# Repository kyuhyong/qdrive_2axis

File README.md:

# QDrive 2axis version

A 2 axis High current BLDC motor controller board based and compatible with Odrive project (https://github.com/madcowswe/ODriveHardware).

Part of this project is based from azmat's single channel BLDC controller board (https://github.com/azmat-bilal/bldc_motor_controller_pcb.git)

## Introduction

<div align="center">
  
</div>

## Odrive compatibility

This project is supposed to be compatible with odrive v3.6-56V.

## Announcement

This project is still in development and need modification to be working as expected.

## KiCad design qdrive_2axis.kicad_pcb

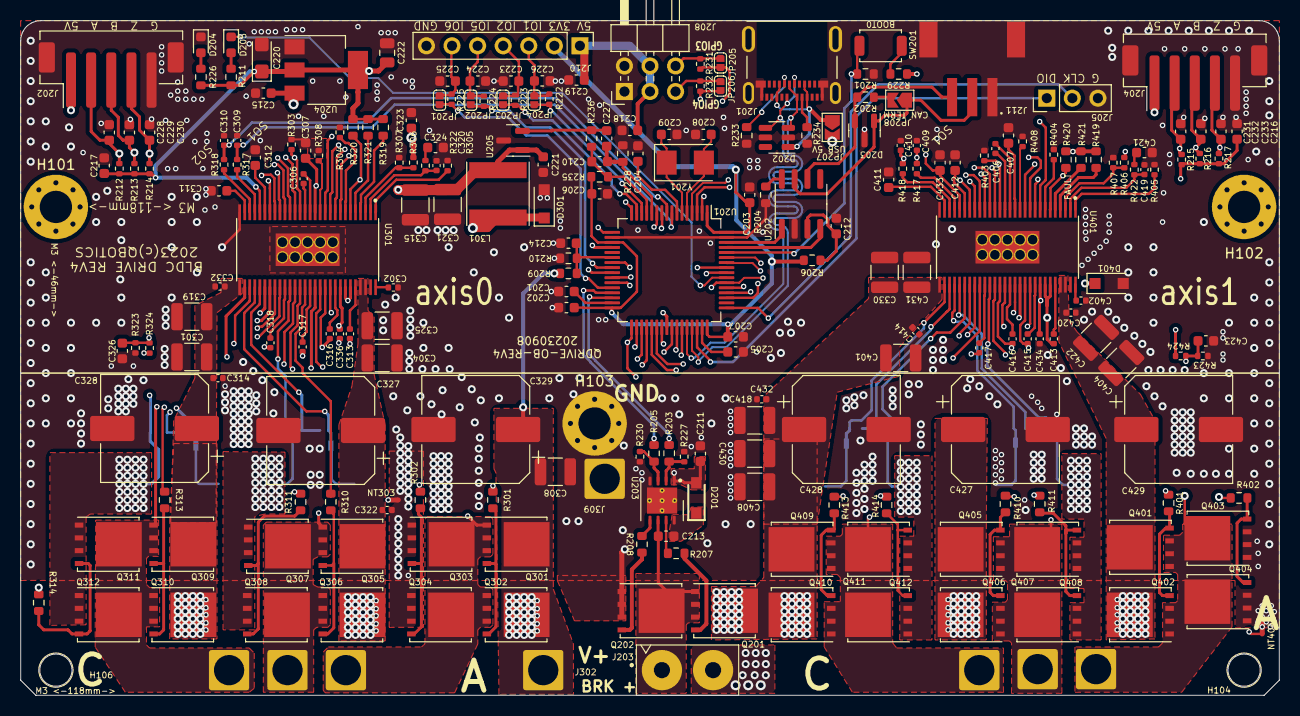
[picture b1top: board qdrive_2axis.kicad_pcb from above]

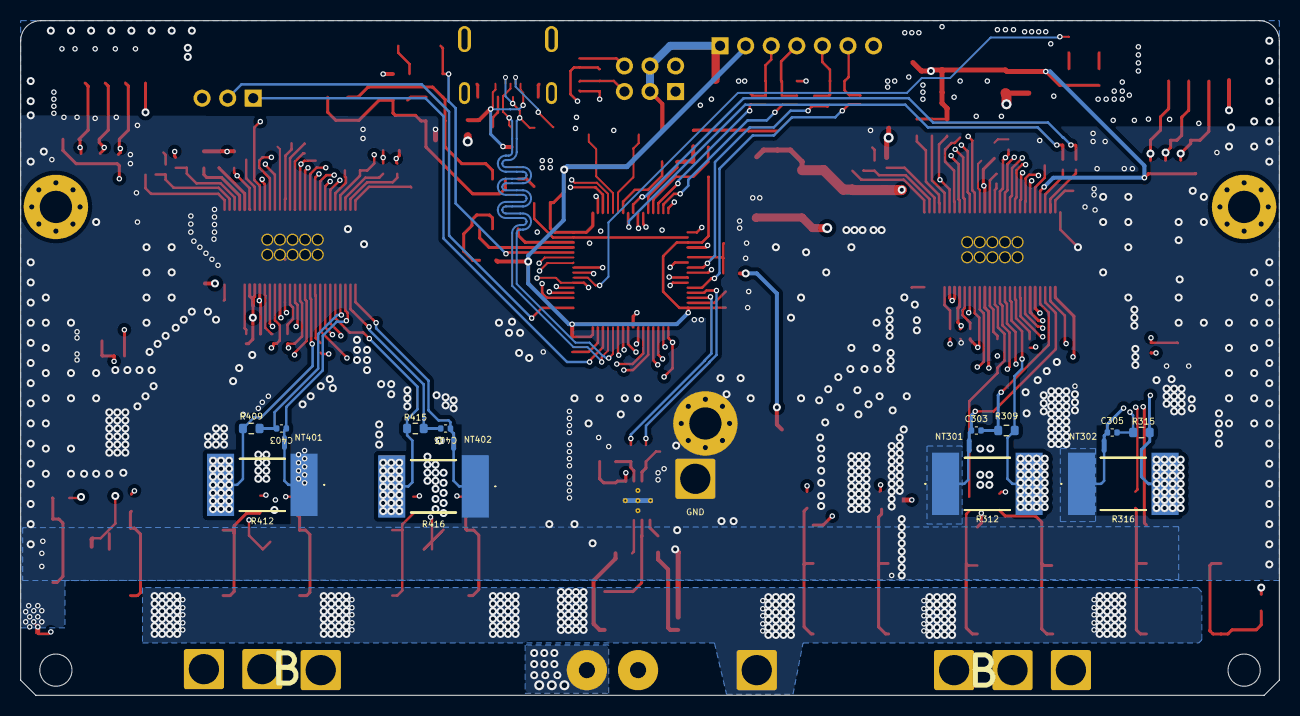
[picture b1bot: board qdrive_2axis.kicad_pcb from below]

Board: 4 copper layers, 125.0 x 67.0 mm, 254 parts (16 on the bottom side), 171 nets.

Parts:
C201, C205, C211, C307, C326, C407, C423: 2.2uF 25V; C_0603_1608Metric
C202, C203, C204, C206, C207, C210, C212, C213, C217, C221, C433: 0.1uF 50V; C_0603_1608Metric
C208, C209: 20pF; C_0603_1608Metric
C214, C324, C421: 270pF; C_0603_1608Metric
C215, C216, C218, C219, C227, C311, C312, C323, C411, C412: 1uF 50V; C_0603_1608Metric
C220: 10uF/10V; CP_EIA-3216-18_Kemet-A
C222: 4.7uF 50V; C_0805_2012Metric
C223, C224, C225, C226: 1nF; C_0603_1608Metric
C228, C229, C230, C231, C232, C233: 22nF 50V; C_0603_1608Metric
C301, C304, C308, C401, C404, C408: 2.2uF 100V; C_1210_3225Metric
C302, C402: 15nF; C_0402_1005Metric
C303, C305, C309, C310, C403, C405, C409, C410: 2200pF; C_0402_1005Metric
C306, C406: 22nF 50V; C_0402_1005Metric
C313, C316, C317, C318, C336, C413, C415, C416, C417, C434: 0.1uF 50V; C_0402_1005Metric
C314, C322, C332, C414, C420, C432: 100nF 100V; C_0402_1005Metric
C315, C321: 22uF 16V; C_1210_3225Metric
C319, C325, C330, C418, C422: 4.7uF 100V; C_1210_3225Metric
C320, C419: 82pF; C_0402_1005Metric
C327, C328, C329, C427, C428, C429: 220uF 50V; CP_Elec_10x14.3
C430, C431: 10uF 63V; C_1210_3225Metric
D201: CRH01; SODFL3516X108N
D202: ESDA6V1BC6; SOT-23-6
D203: SP0502BAHT; SOT-23
D204: LED 1608/RED; LED_0603_1608Metric
D205: LED 1608/GRN; LED_0603_1608Metric
D301, D401: 100V 2A SMB; D_SOD-123F
H101, H102, H103: MountingHole_Pad; MountingHole_3.2mm_M3_Pad_Via
H104, H106: MountingHole_Pad; MountingHole_3.2mm_M3
J201: 1054500101; MOLEX_105450-0101
J202, J204: Conn_01x05_MountingPin; JST_PH_B5B-PH-SM4-TB_1x05-1MP_P2.00mm_Vertical
J203: Screw_Terminal_01x02; TB01050802BE_SMALL
J205: Conn_01x03; PinHeader_1x03_P2.54mm_Vertical
J208: NC_Conn_02x03_Odd_Even; PinHeader_2x03_P2.54mm_Horizontal
J210: NC_Conn_01x07_Female; PinHeader_1x07_P2.54mm_Vertical
J211: S3B-PH-SM4-TB(LF)(SN); JST_S3B-PH-SM4-TB
J301, J302, J306, J307, J309, J401, J402, J403: Screw_Terminal_01x01; SolderWire-2.5sqmm_1x01_D2.4mm_OD3.6mm
JP201, JP202, JP203, JP204, JP205, JP206: SolderJumper_2_Open; SolderJumper-2_P1.3mm_Open_RoundedPad1.0x1.5mm
JP207, JP208: Jumper_2_Open; SolderJumper-2_P1.3mm_Open_TrianglePad1.0x1.5mm
L301: 33uH 1.4A; L_Taiyo-Yuden_NR-60xx
NT301, NT302, NT303, NT401, NT402, NT404: Net-Tie_2; NetTie-2_SMD_Pad0.5mm
Q201, Q202, Q301, Q302, Q303, Q304, Q305, Q306, Q307, Q308, Q309, Q310, Q311, Q312, Q401, Q402, Q403, Q404, Q405, Q406, Q407, Q408, Q409, Q410, Q411, Q412: HYG025N06LS1C2; TDSON-8-1
R201, R210: 1k; R_0603_1608Metric
R202, R211, R226, R309, R315, R409, R415: 120R; R_0603_1608Metric
R203, R205, R206, R228, R229, R236: 0R; R_0603_1608Metric
R204, R319, R320, R321, R419, R420, R421: 10k; R_0603_1608Metric
R207, R208, R301, R302, R310, R311, R313, R314, R401, R402, R410, R411, R413, R414: 2R2; R_0603_1608Metric
R209: 18K; R_0603_1608Metric
R212, R213, R214, R215, R216, R217, R222, R223, R224, R225, R227, R230, R231, R232, R307, R308, R323, R407, R408, R423: 3.3k; R_0402_1005Metric
R233, R234: 5.1K; R_0603_1608Metric
R235: 0R/NC; R_0603_1608Metric
R303, R403: 1k; R_0402_1005Metric
R304, R306, R404, R406: 18k; R_0402_1005Metric
R305, R405: 220K; R_0402_1005Metric
R312, R316, R412, R416: 500uOhm 10W 1%; WSLP3921L5000FEA
R317, R318, R417, R418: 22R 1%; R_0402_1005Metric
R322, R422: 47k 1%; R_0402_1005Metric
R324, R424: 10k; R_0402_1005Metric
SW201: SKRKAHE020; SW_Push_SPST_NO_Alps_SKRK
U201: STM32F405RGT6; LQFP-64_10x10mm_P0.5mm
U202: TJA1050T; SOIC-8_3.9x4.9mm_P1.27mm
U203: LM5109BSD; WSON-8-1EP_4x4mm_P0.8mm_EP2.6x3mm_ThermalVias
U204: LM1117-3.3; SOT-223
U205: NCP51460SN33T1G; SOT-23
U301, U401: DRV8301DCAR; SOP50P810X120-57N
Y201: 8MHz; Crystal_SMD_5032-2Pin_5.0x3.2mm

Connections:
3V3B: C202.2, C203.2, C206.2, C207.2, C216.1, C217.2, C220.1, C222.2, C336.1, C433.1, C434.1, J210.2, R206.1, R211.1, R212.1, R213.1, R214.1, R215.1, R216.1, R217.1, R226.1, R229.2, R235.1, R319.2, R320.2, R321.2, R324.1, R419.2, R420.2, R421.2, R424.1, U201.1 (VBAT), U201.19 (VDD), U201.32 (VDD), U201.48 (VDD), U201.64 (VDD), U204.2 (VO), U204.4 (VO), U301.24 (REF), U301.49 (VDD_SPI), U401.24 (REF), U401.49 (VDD_SPI)
+3.3VA: C210.2, R235.2, R236.2, U201.13 (VDDA)
+5V: C215.1, C218.1, C219.2, C221.2, C315.1, C321.1, C323.1, J202.1, J204.1, J208.3, J208.4, J210.1, JP207.2 (B), L301.2, R306.2, R406.2, U204.3 (VI), U205.1 (Vin)
/M0_axis/AVDD_M0: C311.1, U301.27 (AVDD)
/M0_axis/DVDD_M0: C312.1, U301.23 (DVDD)
/M0_axis/M0B_DC_CAL: R308.2, U301.12 (DC_CAL)
/M0_axis/M0B_EN_GATE: R303.2, R403.2, U201.33 (PB12), U301.16 (EN_GATE), U401.16 (EN_GATE)
/M0_axis/M0B_PWRGD: R319.1, U301.4 (PWRGD)
/M0_axis/M0B_SO1: C309.2, R317.2, U201.8 (PC0)
/M0_axis/M0B_SO2: C310.2, R318.2, U201.9 (PC1)
/M0_axis/M0B_SPI_MISO: U201.52 (PC11), U301.10 (SDO), U401.10 (SDO)
/M0_axis/M0B_SPI_MOSI: U201.53 (PC12), U301.9 (SDI), U401.9 (SDI)
/M0_axis/M0B_SPI_SCK: U201.51 (PC10), U301.11 (SCLK), U401.11 (SCLK)
/M0_axis/M0B_TEMP: C326.1, R323.2, R324.2, U201.25 (PC5)
/M0_axis/M0B_nCS: U201.2 (PC13), U301.8 (~SCS)
/M0_axis/M0BnFAULT: R320.1, R420.1, U201.54 (PD2), U301.6 (~FAULT), U401.6 (~FAULT)
/M0_axis/M0BnOCTW: R321.1, U301.5 (~OCTW)
/M0_axis/M0_GH_A: R301.1, U301.47 (GH_A)
/M0_axis/M0_GH_B: R310.1, U301.42 (GH_B)
/M0_axis/M0_GH_C: R313.1, U301.37 (GH_C)
/M0_axis/M0_GL_A: R302.1, U301.45 (GL_A)
/M0_axis/M0_GL_B: R311.1, U301.40 (GL_B)
/M0_axis/M0_GL_C: R314.1, U301.35 (GL_C)
/M0_axis/M0_SH_A: C316.1, J301.1, Q301.1 (S), Q301.2 (S), Q301.3 (S), Q302.1 (S), Q302.2 (S), Q302.3 (S), Q303.5 (D), Q304.5 (D), U301.46 (SH_A)
/M0_axis/M0_SH_B: C317.1, J306.1, Q305.1 (S), Q305.2 (S), Q305.3 (S), Q306.1 (S), Q306.2 (S), Q306.3 (S), Q307.5 (D), Q308.5 (D), U301.41 (SH_B)
/M0_axis/M0_SH_C: C318.1, J307.1, Q309.1 (S), Q309.2 (S), Q309.3 (S), Q310.1 (S), Q310.2 (S), Q310.3 (S), Q311.5 (D), Q312.5 (D), U301.36 (SH_C)
/M0_axis/M0_SL_A: NT303.1, U301.44 (SL_A)
/M0_axis/M0_SL_B: Q307.1 (S), Q307.2 (S), Q307.3 (S), Q308.1 (S), Q308.2 (S), Q308.3 (S), R309.2, R312.2, U301.39 (SL_B)
/M0_axis/M0_SL_C: Q311.1 (S), Q311.2 (S), Q311.3 (S), Q312.1 (S), Q312.2 (S), Q312.3 (S), R315.2, R316.2, U301.34 (SL_C)
/M0_axis/M0_SN1: C303.2, R309.1, U301.33 (SN1)
/M0_axis/M0_SN2: C305.2, R315.1, U301.31 (SN2)
/M0_axis/M0_SP1: C303.1, NT301.1, U301.32 (SP1)
/M0_axis/M0_SP2: C305.1, NT302.1, U301.30 (SP2)
/M1_axis/AVDD_M1: C411.1, U401.27 (AVDD)
/M1_axis/DVDD_M1: C412.1, U401.23 (DVDD)
/M1_axis/M1B_AH: U201.37 (PC6), U401.17 (INH_A)
/M1_axis/M1B_AL: U201.23 (PA7), U401.18 (INL_A)
/M1_axis/M1B_BH: U201.38 (PC7), U401.19 (INH_B)
/M1_axis/M1B_BL: U201.26 (PB0), U401.20 (INL_B)
/M1_axis/M1B_CH: U201.39 (PC8), U401.21 (INH_C)
/M1_axis/M1B_CL: U201.27 (PB1), U401.22 (INL_C)
/M1_axis/M1B_DC_CAL: R408.2, U401.12 (DC_CAL)
/M1_axis/M1B_PWRGD: R419.1, U401.4 (PWRGD)
/M1_axis/M1B_SO1: C409.2, R417.2, U201.11 (PC3)
/M1_axis/M1B_SO2: C410.2, R418.2, U201.10 (PC2)
/M1_axis/M1B_TEMP: C423.1, R423.2, R424.2, U201.20 (PA4)
/M1_axis/M1B_nCS: U201.3 (PC14), U401.8 (~SCS)
/M1_axis/M1BnOCTW: R421.1, U401.5 (~OCTW)
/M1_axis/M1_GH_A: R401.1, U401.47 (GH_A)
/M1_axis/M1_GH_B: R410.1, U401.42 (GH_B)
/M1_axis/M1_GH_C: R413.1, U401.37 (GH_C)
/M1_axis/M1_GL_A: R402.1, U401.45 (GL_A)
/M1_axis/M1_GL_B: R411.1, U401.40 (GL_B)
/M1_axis/M1_GL_C: R414.1, U401.35 (GL_C)
/M1_axis/M1_SH_A: C415.2, J401.1, Q401.1 (S), Q401.2 (S), Q401.3 (S), Q402.1 (S), Q402.2 (S), Q402.3 (S), Q403.5 (D), Q404.5 (D), U401.46 (SH_A)
/M1_axis/M1_SH_B: C416.2, J402.1, Q405.1 (S), Q405.2 (S), Q405.3 (S), Q406.1 (S), Q406.2 (S), Q406.3 (S), Q407.5 (D), Q408.5 (D), U401.41 (SH_B)
/M1_axis/M1_SH_C: C417.2, J403.1, Q409.1 (S), Q409.2 (S), Q409.3 (S), Q410.1 (S), Q410.2 (S), Q410.3 (S), Q411.5 (D), Q412.5 (D), U401.36 (SH_C)
/M1_axis/M1_SL_A: NT404.1, U401.44 (SL_A)
/M1_axis/M1_SL_B: Q407.1 (S), Q407.2 (S), Q407.3 (S), Q408.1 (S), Q408.2 (S), Q408.3 (S), R409.2, R412.2, U401.39 (SL_B)
/M1_axis/M1_SL_C: Q411.1 (S), Q411.2 (S), Q411.3 (S), Q412.1 (S), Q412.2 (S), Q412.3 (S), R415.2, R416.2, U401.34 (SL_C)
/M1_axis/M1_SN1: C403.2, R409.1, U401.33 (SN1)
/M1_axis/M1_SN2: C405.2, R415.1, U401.31 (SN2)
/M1_axis/M1_SP1: C403.1, NT401.1, U401.32 (SP1)
/M1_axis/M1_SP2: C405.1, NT402.1, U401.30 (SP2)
/MCU/AUX_N: R205.1, U201.29 (PB10)
/MCU/AUX_P: R203.1, U201.30 (PB11)
/MCU/BOOT0: R201.2, SW201.1 (A), U201.60 (BOOT0)
/MCU/BRAKE_OUT: C213.1, J203.1, Q201.1 (S), Q201.2 (S), Q201.3 (S), Q202.5 (D), U203.6 (HS)
/MCU/CAN1_H: D203.1 (K), J211.2, JP208.1 (A), U202.7 (CANH)
/MCU/CAN1_L: D203.2 (K), J211.3, R202.2, U202.6 (CANL)
/MCU/CAN_D: U201.62 (PB9), U202.1 (TXD)
/MCU/CAN_R: U201.61 (PB8), U202.4 (RXD)
/MCU/GPIO_1: JP204.1 (A), R222.1, U201.14 (PA0)
/MCU/GPIO_2: JP203.1 (A), R223.1, U201.15 (PA1)
/MCU/GPIO_3: JP205.1 (A), R231.1, U201.16 (PA2)
/MCU/GPIO_4: JP206.2 (B), R232.2, U201.17 (PA3)
/MCU/GPIO_5: JP202.1 (A), R224.1, U201.24 (PC4)
/MCU/GPIO_6: JP201.1 (A), R225.1, U201.28 (PB2)
/MCU/GPIO_8: D205.1 (K), U201.55 (PB3)
/MCU/M0_AH: U201.41 (PA8), U301.17 (INH_A)
/MCU/M0_AL: U201.34 (PB13), U301.18 (INL_A)
/MCU/M0_BH: U201.42 (PA9), U301.19 (INH_B)
/MCU/M0_BL: U201.35 (PB14), U301.20 (INL_B)
/MCU/M0_CH: U201.43 (PA10), U301.21 (INH_C)
/MCU/M0_CL: U201.36 (PB15), U301.22 (INL_C)
/MCU/M0_ENC_A: C228.1, J202.2, R212.2, U201.56 (PB4)
/MCU/M0_ENC_B: C229.1, J202.3, R213.2, U201.57 (PB5)
/MCU/M0_ENC_Z: C230.1, J202.4, R214.2, U201.40 (PC9)
/MCU/M1_ENC_A: C231.1, J204.2, R215.2, U201.58 (PB6)
/MCU/M1_ENC_B: C232.1, J204.3, R216.2, U201.59 (PB7)
/MCU/M1_ENC_Z: C233.1, J204.4, R217.2, U201.4 (PC15)
/MCU/OSC_IN: C208.2, U201.5 (PH0), Y201.2
/MCU/OSC_OUT: C209.2, U201.6 (PH1), Y201.1
/MCU/SWCLK: J205.2, U201.49 (PA14)
/MCU/SWDIO: J205.1, U201.46 (PA13)
/MCU/USB_D+: D202.3 (TVS2), J201.A6 (DP1), J201.B6 (DP2), U201.45 (PA12)
/MCU/USB_D-: D202.4 (TVS3), J201.A7 (DN1), J201.B7 (DN2), U201.44 (PA11)
/MCU/USB_V: D202.1 (TVS1), J201.A4 (VBUS_1), J201.A9 (VBUS_2), J201.B4 (VBUS_3), J201.B9 (VBUS_4), JP207.1 (A)
/MCU/VBUS_S: C214.1, R209.1, R210.2, U201.22 (PA6)
/MCU/nRST: C204.1, U201.7 (NRST)
GND: C201.1, C202.1, C203.1, C204.2, C205.1, C206.1, C207.1, C208.1, C209.1, C211.2, C212.1, C214.2, C215.2, C216.2, C217.1, C218.2, C219.1, C220.2, C221.1, C222.1, C223.1, C224.1, C225.1, C226.1, C228.2, C229.2, C230.2, C231.2, C232.2, C233.2, C301.2, C302.2, C304.2, C307.1, C308.2, C309.1, C310.1, C311.2, C312.2, C314.2, C315.2, C319.2, C320.2, C321.2, C322.2, C323.2, C324.2, C325.2, C326.2, C327.2, C328.2, C329.2, C330.2, C332.2, C336.2, C401.2, C402.1, C404.2, C407.2, C408.2, C409.1, C410.1, C411.2, C412.2, C414.2, C418.2, C419.2, C420.2, C421.2, C422.2, C423.2, C427.2, C428.2, C429.2, C430.2, C431.2, C432.2, C433.2, C434.2, D202.2 (COM), D202.5 (COM), D203.3 (A), D204.1 (K), D301.2 (A), D401.2 (A), H103.1, J201.A1 (GND_1), J201.A12 (GND_2), J201.B1 (GND_3), J201.B12 (GND_4), J201.MH1, J201.MH2, J201.MH3, J201.MH4, J202.5, J202.MP (MountPin), J203.2, J204.5, J204.MP (MountPin), J205.3, J208.1, J208.2, J210.7, J211.1, J211.MP (MountPin), J309.1, NT301.2, NT302.2, NT303.2, NT401.2, NT402.2, NT404.2, Q202.1 (S), Q202.2 (S), Q202.3 (S), Q303.1 (S), Q303.2 (S), Q303.3 (S), Q304.1 (S), Q304.2 (S), Q304.3 (S), Q403.1 (S), Q403.2 (S), Q403.3 (S), Q404.1 (S), Q404.2 (S), Q404.3 (S), R201.1, R204.1, R210.1, R227.2, R228.2, R230.2, R233.1, R234.1, R303.1, R304.2, R305.2, R307.1, R308.1, R312.1, R316.1, R323.1, R403.1, R404.2, R405.2, R407.1, R408.1, R412.1, R416.1, R423.1, U201.18 (VSS), U201.63 (VSS), U202.2 (GND), U203.4 (VSS), U203.9 (VSS), U204.1 (GND), U205.3 (Vss), U301.28 (AGND), U301.57 (GND), U401.28 (AGND), U401.57 (GND)
GNDA: C210.1, C227.2, R228.1, U201.12 (VSSA)
GVDD_M0: C211.1, C307.2, D201.2 (A), U203.1 (VDD), U301.13 (GVDD)
GVDD_M1: C407.1, U401.13 (GVDD)
unnamed: C324.1, R322.2
unnamed: C421.1, R422.2
unnamed: C213.2, D201.1 (K), U203.8 (HB)
unnamed: D204.2 (A), R226.2
unnamed: D205.2 (A), R211.2
unnamed: C313.2, D301.1 (K), L301.1, U301.50 (PH), U301.51 (PH)
unnamed: C413.2, D401.1 (K), U401.50 (PH), U401.51 (PH)
unnamed: J201.A5 (CC1), R234.2
unnamed: J201.B5 (CC2), R233.2
unnamed: J208.5, JP206.1 (A), R232.1
unnamed: J208.6, JP205.2 (B), R231.2
unnamed: C226.2, J210.3, JP204.2 (B), R222.2
unnamed: C223.2, J210.4, JP203.2 (B), R223.2
unnamed: C224.2, J210.5, JP202.2 (B), R224.2
unnamed: C225.2, J210.6, JP201.2 (B), R225.2
unnamed: JP208.2 (B), R202.1
unnamed: Q201.4 (G), R207.2
unnamed: Q202.4 (G), R208.2
unnamed: Q301.4 (G), Q302.4 (G), R301.2
unnamed: Q303.4 (G), Q304.4 (G), R302.2
unnamed: Q305.4 (G), Q306.4 (G), R310.2
unnamed: Q307.4 (G), Q308.4 (G), R311.2
unnamed: Q309.4 (G), Q310.4 (G), R313.2
unnamed: Q311.4 (G), Q312.4 (G), R314.2
unnamed: Q401.4 (G), Q402.4 (G), R401.2
unnamed: Q403.4 (G), Q404.4 (G), R402.2
unnamed: Q405.4 (G), Q406.4 (G), R410.2
unnamed: Q407.4 (G), Q408.4 (G), R411.2
unnamed: Q409.4 (G), Q410.4 (G), R413.2
unnamed: Q411.4 (G), Q412.4 (G), R414.2
unnamed: R229.1, SW201.2 (B)
unnamed: C201.2, U201.31 (VCAP_1)
unnamed: C205.2, U201.47 (VCAP_2)
unnamed: R204.2, U202.8 (S)
unnamed: C212.2, R206.2, U202.3 (VCC)
unnamed: R203.2, R227.1, U203.2 (HI)
unnamed: R207.1, U203.7 (HO)
unnamed: R205.2, R230.1, U203.3 (LI)
unnamed: R208.1, U203.5 (LO)
unnamed: C227.1, R236.1, U205.2 (Vout)
unnamed: C316.2, U301.48 (BST_A)
unnamed: C317.2, U301.43 (BST_B)
unnamed: C313.1, U301.52 (BST_BK)
unnamed: C318.2, U301.38 (BST_C)
unnamed: C320.1, R322.1, U301.2 (COMP)
unnamed: C306.1, U301.14 (CP1)
unnamed: C306.2, U301.15 (CP2)
unnamed: R304.1, U301.7 (DTC)
unnamed: R305.1, U301.1 (RT_CLK)
unnamed: R317.1, U301.25 (SO1)
unnamed: R318.1, U301.26 (SO2)
unnamed: C302.1, U301.56 (SS_TR)
unnamed: R306.1, R307.2, U301.3 (VSENSE)
unnamed: C415.1, U401.48 (BST_A)
unnamed: C416.1, U401.43 (BST_B)
unnamed: C413.1, U401.52 (BST_BK)
unnamed: C417.1, U401.38 (BST_C)
unnamed: C419.1, R422.1, U401.2 (COMP)
unnamed: C406.1, U401.14 (CP1)
unnamed: C406.2, U401.15 (CP2)
unnamed: R404.1, U401.7 (DTC)
unnamed: R405.1, U401.1 (RT_CLK)
unnamed: R417.1, U401.25 (SO1)
unnamed: R418.1, U401.26 (SO2)
unnamed: C402.2, U401.56 (SS_TR)
unnamed: R406.1, R407.2, U401.3 (VSENSE)
VPP_M0: C301.1, C304.1, C308.1, C314.1, C319.1, C322.1, C325.1, C327.1, C328.1, C329.1, C330.1, C332.1, C401.1, C404.1, C408.1, C414.1, C418.1, C420.1, C422.1, C427.1, C428.1, C429.1, C430.1, C431.1, C432.1, J302.1, Q201.5 (D), Q301.5 (D), Q302.5 (D), Q305.5 (D), Q306.5 (D), Q309.5 (D), Q310.5 (D), Q401.5 (D), Q402.5 (D), Q405.5 (D), Q406.5 (D), Q409.5 (D), Q410.5 (D), R209.2, U301.29 (PVDD1), U301.53 (PVDD2), U301.54 (PVDD2), U401.29 (PVDD1), U401.53 (PVDD2), U401.54 (PVDD2)

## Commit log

2023-12-12 Fixed mounting holes
2023-12-12 Fixes
